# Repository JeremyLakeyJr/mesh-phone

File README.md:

# MESH-PHONE

ESP32-S3 handheld hardware with sub-GHz radios, LTE, NFC/RFID, a 4×4 keypad,
trackball, GPS and a rear expansion connector. Engineering prototype. **DO NOT FABRICATE OR POWER:** the current handset
is incomplete and only partially routed.

## Project layout

| Directory | Contents |
|---|---|
| [hardware/rev-f](hardware/rev-f/README.md) | Preserved GPS/expansion revision; superseded by the handset redesign |
| [hardware/handset-rev-a](hardware/handset-rev-a/README.md) | Active handset PCB and schematic; open `generated/handset.kicad_pro` |
| `hardware/main/` | Preserved original KiCad project and its local footprints |
| [mechanical/handset](mechanical/handset/README.md) | Latest reference-inspired handset concept; requires new PCB |
| [mechanical/enclosure](mechanical/enclosure/README.md) | Preserved enclosure for the existing Rev F board |
| `scripts/` | Maintained geometry extraction and revision verification |
| `docs/design/` | Historical design notes, pin budgets and routing notes |
| `docs/reviews/` | Electrical review evidence |
| `manufacturing/` | BOMs and explicitly unreleased legacy fabrication exports |
| `archive/` | Prior PCB candidates, enclosure and one-off development scripts |

## Working with the project

Open `hardware/handset-rev-a/generated/handset.kicad_pro` in KiCad 10.
Keep its local symbol and footprint libraries beside the project. The current
checkpoint was checked with KiCad 10.0.6.

Run `bash scripts/check_handset_pcb.sh` to refresh the native netlist, ERC/DRC,
connectivity checks, schematic PDF and previews. Then run
`python3 scripts/check_handset_release.py` to evaluate the release gate.
**The release gate currently fails intentionally:** passing artifact-integrity
checks does not mean the electronics are ready to manufacture.

For the preserved Rev F project, `python3 scripts/verify_revF.py` checks its saved
netlist and placement contracts; it does not run fresh native electrical analysis.

Run `python scripts/enclosure_geometry.py` after PCB mechanical changes, then
`scripts/export_enclosure.sh` to rebuild the enclosure STLs and preview.
See the mechanical README for panel-placement assumptions and fit checks.

Archived scripts preserve historical experiments, including obsolete absolute
paths and old project names. They are not a supported build pipeline and should
not be replayed on the active board. `.history/` is the existing KiCad history
repository and remains in place.

The current enclosure has a sculpted rear, rounded corners and a rolled front
rim. Its maximum body envelope remains 74 × 154 × 26 mm; populated-board fit
and the detachable modem pod still need engineering validation.

Latest appearance: [handset preview](mechanical/handset/exports/design-preview.png).
See [feature preservation](mechanical/handset/FEATURES.md) for the retained hardware
requirements and explicit packaging changes. Build with `scripts/export_handset.sh`.
The selected new-board materials list is in
[`hardware/handset-rev-a/materials-to-use.csv`](hardware/handset-rev-a/materials-to-use.csv).
The supporting component research and comparison table are in
[`docs/research/new-pcb-component-study.md`](docs/research/new-pcb-component-study.md)
and [`hardware/handset-rev-a/candidate-components.csv`](hardware/handset-rev-a/candidate-components.csv).

## Fabrication readiness checklist

Checkpoint: **2026-10-13**. Checked items mean the stated design-file work is
complete, not that the hardware has passed bench testing. Current status:
**277 schematic components, 2,644 passing integrity checks, zero schematic/PCB
parity findings, 20 ERC findings, zero DRC findings, and
142 unconnected items.** Eleven engineering blocker groups remain open.
The detailed source of truth is
[release-blockers.json](hardware/handset-rev-a/release-blockers.json).

Current priority is prototype fabrication readiness: complete the missing circuits,
finish copper and return paths, clear ERC/DRC, freeze the BOM and mechanical fit,
and obtain fabricator/assembler DFM review. Firmware feature work follows this
hardware work. Bench qualification remains required after prototype assembly.

### Completed design work

- [x] Route SX1262 SPI, chip select and pull-up, reset, BUSY and DIO1. Twelve checks and 17 regression cases pass; native DRC/parity remain clear. [Digital checkpoint](hardware/handset-rev-a/sx1262-power-review.md#digital-interface-checkpoint--2026-10-13).

- [x] Route the CC1101 SPI, chip-select pull-up, GDO0 and GDO2 test point. Thirteen checks and 15 regression cases pass; native DRC/parity remain clear. [Digital checkpoint](hardware/handset-rev-a/cc1101-review.md#digital-interface-checkpoint--2026-10-12).

- [x] Route the SX1262 switch, three RF DC blocks, antenna connector, control filter and filtered supply. Seventeen regression cases and 753 reference samples pass; RF performance remains unqualified. [Switched RF checkpoint](hardware/handset-rev-a/sx1262-power-review.md#switched-rf-routing-checkpoint--2026-10-10).

- [x] Ground all five SX1262 matching-device return lands using scoped 0.2 mm drilled vias and local copper. Thirteen regression cases pass; record a screened 0.34 mm downstream RF routing target. [Ground/impedance checkpoint](hardware/handset-rev-a/sx1262-power-review.md#rf-ground-and-impedance-checkpoint--2026-10-10).
- [x] Relocate the SX1262 clock and route local PA/RF input connections. Nine copper regression cases pass; RF qualification stays open. [Local routing checkpoint](hardware/handset-rev-a/sx1262-power-review.md#local-parf-routing-checkpoint--2026-10-09).
- [x] Capture SX1262 PA choke and dual bypass with specified parts. Eleven circuit mutations pass; PA/RF electrical qualification remains open. [PA checkpoint](hardware/handset-rev-a/sx1262-power-review.md#pa-choke-and-bypass-checkpoint--2026-10-08).
- [x] Capture SX1262 matching/filter, TX/RX switch, control/supply filters and DC blocks. Eight wrong-wiring/value tests pass; physical copper follows in the switched RF checkpoint. [RF checkpoint](hardware/handset-rev-a/sx1262-power-review.md#rf-matching-and-switch-checkpoint--2026-10-08).
- [x] Connect SX1262 input supplies, bypass capacitors and all ground pins to the established rail/return network. Six open-pad tests and 16-pad continuity pass. [Supply checkpoint](hardware/handset-rev-a/sx1262-power-review.md#input-supply-routing-checkpoint--2026-10-08).
- [x] Route the SX1262 core regulator loop, VREG capacitor return and regulator/exposed-pad ground. Six open-pad controls pass; 15 copper items added with existing copper preserved. [Regulator checkpoint](hardware/handset-rev-a/sx1262-power-review.md#regulator-routing-checkpoint--2026-10-08).
- [x] Capture and route the SX1262 TCXO clock: 14 pads, an 8.092 mm relocated clock path and its ground reference pass checks. ERC falls by three; RF frontend and clock electrical qualification remain open. [Clock checkpoint](hardware/handset-rev-a/sx1262-power-review.md#tcxo-clock-checkpoint--2026-10-08).

- [x] Route amplifier power, ground and local shutdown bias; move C13 beside U6. Fifteen physical pads pass continuity, five regression cases pass, and existing copper remains intact. Speaker/I²S/microphone routing remains open. [Layout checkpoint](hardware/handset-rev-a/README.md#audio-power-routing-checkpoint).

- [x] Cross-build an ESP32-S3 keypad bring-up application with I²C, GPIO8 interrupts, USB logs and start/stop/recovery commands. Twelve session tests and native pin-map checks pass. [Build and commissioning instructions](firmware/bringup/README.md); hardware testing remains open.
- [x] Complete the 16-key matrix copper (72 physical pads), add five routing regression cases and a host-tested keypad driver with overflow recovery. [Routing and firmware evidence](hardware/handset-rev-a/keypad-routing-review.md).
- [x] Route ESP32 boot/reset service controls and U2 power, reset, I²C and interrupt connections; eight regression cases pass with zero DRC/parity findings. [Evidence and remaining bring-up work](hardware/handset-rev-a/core-bringup-review.md).
- [x] Organize hardware, mechanical designs, research, reviews and archived checkpoints.
- [x] Create the four-layer handset PCB and rebuild the schematic as a system index plus 24 functional sheets.
- [x] Retain ESP32-S3-WROOM-1-N16R8 and preserve interfaces for the external display, keypad, trackball, cellular adapter, radios, GNSS, NFC/LF RFID, storage, IR, audio and expansion.
- [x] Capture MakerFocus 3000 mAh battery requirements and the external-module connector; exact pack qualification remains below.
- [x] Populate the current schematic/PCB with component footprints and a materials list; final BOM and footprint audits remain below.
- [x] Capture BQ25186 charging, fused USB/battery entry, TPS25200 protection, TUSB320LAI source detection and TCA9536 controls; verify continuity of 113 local power-entry pads.
- [x] Cross-build and validate an inhibited STM32G031 commissioning image with private-bus I²C, PA0 shutdown, watchdog and diagnostic host interface. [Build, evidence and limits](firmware/power/stm32g031/README.md).
- [x] Route supervisor power, private/host I²C and SWD connections; verify 67 endpoints and preserve existing copper. [Routing evidence and remaining work](hardware/handset-rev-a/supervisor-routing-review.md).
- [x] Route charger VSYS to U7, the main power-switch control, and U7 to ESP32 power/bypass/ground; verify 38 physical pads with no new DRC findings. [Routing evidence and limits](hardware/handset-rev-a/main-distribution-review.md).
- [x] Add and route independent STM32 charge permission so a retained expander output cannot defeat reset inhibition; update controller sequencing and pass topology, continuity and fault tests. [Design and qualification limits](hardware/handset-rev-a/charge-inhibit-review.md).
- [x] Capture and place the separate STM32G031 charging supervisor, always-on regulator and isolated host bus; preserve existing copper geometry. [Circuit and remaining work](hardware/handset-rev-a/power-supervisor-review.md).
- [x] Record the charger-policy contract and implement a host-tested portable charger controller with a 4.17 V target; STM32 supervisor integration and hardware tests remain below.
- [x] Capture published MakerFocus pack specifications and calculate an illustrative modem-load budget; the current pack/modem compatibility blocker remains open.
- [x] Audit modem startup/output tolerance and battery current directly from CAD; add regression tests and release-gate checks. User selected a higher-current ~3000 mAh pack; provisional target is at least 5 A, with pack/fit/F2/J1 qualification still open. [Power review and battery requirements](hardware/handset-rev-a/modem-power-review.md).
- [x] Screen a concrete higher-current pouch and low-profile connector: CU-JAS427 and Molex 2053380002. Pack current clears the provisional calculation, but fit and production qualification fail; neither is frozen. [Candidate evidence and remaining checks](hardware/handset-rev-a/battery-candidate-review.md).
- [x] Replace J1 with the low-profile Molex 2053380002 in schematic and PCB; repair local battery/ground routing, preserve unrelated layout, and verify 118 power-entry pads plus a broken-route negative test. [Connector implementation and fuse screening](hardware/handset-rev-a/battery-connector-review.md).
- [x] Widen the battery-to-fuse main trace to 1.2 mm where clearance permits; reduce its calculated resistance by about 24%, preserve placement, and verify continuity with a broken-trace test. Fuse selection and current/thermal qualification remain open. [Copper and fuse follow-up](hardware/handset-rev-a/battery-copper-review.md).
- [x] Inventory handset loads and add a 60-case battery-only power-envelope check separating the charger-fed handset from the modem. Flag the incomplete 0.25 A allowance and configured handset discharge limit in the release gate. [System power review](hardware/handset-rev-a/system-power-review.md).
- [x] Audit display/backlight and expansion limits; specify four high-power backlight resistors in schematic, PCB and BOM. Add checks for panel supply tolerance and port current limit. [Display and expansion review](hardware/handset-rev-a/display-expansion-power-review.md).
- [x] Capture and place a dedicated 3.0 V display supply, SPI/control buffers and touch I²C translator using specified parts. Preserve shared-bus MISO deselection; update BOM and power inventory. Physical routing is recorded below; electrical qualification remains open. [Display interface review](hardware/handset-rev-a/display-interface-review.md).
- [x] Route and physically verify the dedicated display interface: 25 net groups, including supplies, host/connector signals and grounds. Preserve existing placement/copper; add ground returns and continuity regression tests. [Display routing review](hardware/handset-rev-a/display-routing-review.md).
- [x] Install and route the CAT4004A backlight current driver, replacing Q2/R52–R55; verify 26 endpoints, seven regression tests and no new DRC findings. Preserve existing display continuity. [Implementation and qualification limits](hardware/handset-rev-a/backlight-routing-review.md).
- [x] Capture and route expansion power control, fault sensing and hardware signal isolation; verify 31 physical net groups and six regression tests, and add a host-tested portable controller. Preserve all 4,183 existing copper items. [Implementation and qualification limits](hardware/handset-rev-a/expansion-control-review.md).
- [x] Improve expansion ESD ground returns with local inner-layer pours and a direct U16 ground bridge; remove 36.24 mm of ground detours, preserve all signal routing and pass ground-return regression tests. [Evidence and remaining limits](hardware/handset-rev-a/expansion-control-review.md).
- [x] Clear all four USB connector hole-clearance findings using a dedicated ground-corner-relief footprint; preserve holes, routed copper and board rules. Native DRC is now zero; four geometry regression tests pass. [Footprint change and remaining qualification](hardware/handset-rev-a/usb-connector-review.md).
- [x] Route both USB-C data orientations through ESD protection and 22 Ω host termination; match CAD path lengths, add reference copper and verify seven regression cases. Record the JLC04161H-7628 stackup target; fabricator impedance and electrical qualification remain open. [Routing evidence and limits](hardware/handset-rev-a/usb-data-routing-review.md).
- [x] Route the local TPS63802 main 3.3 V regulator circuit; verify continuity of 26 pads.
- [x] Route U20 local modem converter, feedback, ground and switch-controlled enable network; verify 48 pads with no new DRC findings. [Layout and startup limits](hardware/handset-rev-a/modem-layout-review.md).
- [x] Route U10 local 5 V boost, feedback, ground and switch enable; verify 19 pads with no new DRC findings. [Layout and voltage limits](hardware/handset-rev-a/reg5-layout-review.md).
- [x] Route U10 VSYS feed and LF RFID power/ground for U9/U18; verify 36 pads and preserve existing copper. [Distribution evidence and limits](hardware/handset-rev-a/reg5-distribution-review.md).
- [x] Route the local U11 1.8 V regulator circuit, reposition input bypass and orient the inductor toward SW; verify 15 pads and preserve existing copper. [Layout evidence and remaining qualification](hardware/handset-rev-a/reg18-layout-review.md).
- [x] Connect U7 to U11 input, shorten C28 output/sense paths and verify 17 pads. Audit confirms no external 1.8 V loads are assigned; rail purpose remains open. [Distribution evidence](hardware/handset-rev-a/reg18-distribution-review.md).
- [x] Capture auxiliary supplies and the regulated modem supply/enable circuit; complete routing and load qualification remain below.
- [x] Capture the CC1101 clock, 868/915 MHz matching/filter, supply bypass and GDO2 test pad; pass 90 topology/value checks and five negative tests.
- [x] Add SX1262 core DC-DC support, correct its VREG capacitor to 470 nF, and specify input bypass parts; pass 30 circuit checks and four negative tests.
- [x] Capture GNSS, display/touch/backlight, audio, storage/IR, NFC/LF support and protected expansion interfaces; incomplete support circuits are listed below.
- [x] Preserve prior CAD checkpoints and existing routed copper during staged updates.
- [x] Add repeatable checks, schematic PDF and board/assembly previews. Current placement checks report no overlaps; fabrication release remains blocked.

### Remaining before first prototype fabrication

Work through these in order; circuit and mechanical decisions must be resolved
before final routing and manufacturing exports.

- [ ] **Battery and charging:** qualify a higher-current ~3000 mAh 1S replacement (provisional ≥5 A target), preserving the pocketable design; verify dimensions, polarity, protection, NTC and charge/discharge limits. Re-select F2 and qualify J1/harness/copper for the full handset/modem current budget. Complete STM32 durable fault storage, service rearm and expiring host permissions, qualify reset-time CE inhibition and powered-off charging. Confirm NTC attachment and charge-temperature limits. Implement charger policy, fault handling and source recovery; qualify the routed supervisor power/control buses and finish remaining system distribution.
- [ ] **Power supplies:** finish U7 distribution to the remaining peripheral loads and U20 external battery/modem distribution; resolve the audited 3.71–4.13 V turn-on range (up to 4.21 V with the EN-current screening allowance); qualify the routed U10 display branch for voltage, current and trace sizing; resolve the unused 1.8 V rail (assign justified loads or remove it), then finalize U11 output/sense layout. Calculate worst-case inductor current, capacitor DC bias, feedback tolerance, thermal dissipation, startup/UVLO and modem burst margin. Define current-limited bring-up limits and test points.
- [ ] **Cellular adapter:** freeze an orderable modem variant, firmware, SIM interface, logic translation and call-audio circuit. Verify supported bands and carrier VoLTE requirements; interchangeable adapters do not guarantee every carrier. Select the call microphone and speaker/harness arrangement.
- [ ] **SX1262 LoRa:** qualify the captured 32 MHz TCXO amplitude, DIO3 supply and startup timing; qualify the routed PA choke/bypass and local RF input geometry; qualify matching-device grounds, routed RF switch/antenna paths and all three signal-via transitions; complete thermal layout; qualify the routed input supplies and core regulator loop.
- [ ] **CC1101:** qualify shared-SPI/GDO timing, inner-layer return paths and the routed oscillator, bypass, balun/filter and separate antenna feed against the selected stackup. Review crystal load/drive, thermal-via assembly and the optional spur filter; define firmware SPI/GDO configuration.
- [ ] **NFC and LF RFID:** finish ST25R3916B matching/receive circuitry and HTRC110 clock, analog reference, coil network and timing-capable host return path. Specify external coils, crystal loading and tuning provisions.
- [ ] **GNSS:** finish MAX-M10S decoupling and RF feed; select the passive antenna and verify mounting, keepouts and coexistence requirements.
- [ ] **Expansion and USB:** qualify routed J16 current limits, inrush, isolation, ESD return paths, fault recovery and shared-bus timing; integrate the portable controller. Exchange modules only with handset power off. Qualify the routed USB fanout, uncoupled tuning, three via transitions per leg, termination and eye performance; obtain fabricator impedance approval. Obtain assembler DFM approval of the USB4105 relieved ground-land contour and qualify connector fit/solder joints.
- [ ] **Display, controls and peripherals:** next, qualify the routed U28–U31 interface for regulator load/heat, trace sizing, capacitor DC bias, power sequencing and shared-bus timing; qualify the routed CAT4004A backlight current, heat and default-off/on sequencing. Confirm the purchased display/touch configuration, FPC contact orientation, supply/backlight requirements and GPIO budget. Review keypad-scanner controls, shared SPI chip selects, IR boot behavior, microSD and audio interfaces; implement the firmware needed for safe bring-up.
- [ ] **Antennas and coexistence:** select actual LTE, LoRa, CC1101, GNSS and Wi-Fi/BLE antenna arrangements, cable/connectors and matching provisions. Establish ground clearance, spacing and simultaneous-transmit policy; retain access for RF measurements.
- [ ] **BOM and footprints:** freeze all orderable parts with tolerance, voltage, power, dielectric, temperature and lifecycle requirements. Independently audit every custom symbol pin map, package, exposed pad, paste pattern, orientation and connector mating direction. Define DNP options and approved substitutions.
- [ ] **Mechanical fit:** reconcile the PCB with the pocketable case, actual battery, external screen/FPC, trackball opening and retention, top speaker, bottom microphone, antennas, mounting hardware and external module port. Check populated heights, cable bends and moved power-switch access using a full assembly model and fit prototype.
- [ ] **Fabricator rules:** confirm the proposed JLC04161H-7628 four-layer stackup, copper weights, impedance targets, drill/via limits, solder-mask rules and ESP32 and expansion J16.8/U14.1/U14.6/U16.1 via-in-pad filling/capping requirements with the chosen fabricator. Resolve RF reference via sizes against those capabilities.
- [ ] **Complete PCB routing:** connect all 142 currently unconnected items; finish return planes, ground stitching, thermal paths and supply distribution. Review switching loops, RF/USB impedance, antenna keepouts and analog/digital interference. Recheck clearances after all placement changes.
- [ ] **Independent electrical review:** check every pin and power state against manufacturer documents, including boot straps, pull resistors, power sequencing, unpowered interfaces and test access. Close each blocker with evidence rather than marking an incomplete subsystem complete.
- [ ] **Final native checks:** regenerate netlist/ERC/DRC from the exact release revision; resolve the 30 current ERC findings and all airwires; retain zero DRC findings. Require zero parity errors and passing circuit/continuity checks. Any genuinely intentional rule exception needs a documented engineering justification, not a blanket waiver.
- [ ] **Prototype manufacturing package:** export and inspect Gerbers, plated/non-plated drill files, fabrication drawing/stackup, assembly drawings, full MPN BOM, DNP list and pick-and-place files. Verify units, origin, bottom-side rotation, pin 1, polarity and layer alignment in an independent viewer; obtain fabricator/assembler DFM feedback.
- [ ] **Prototype release:** review the complete package and bring-up plan, close the applicable prototype blockers, tag the exact Git revision and archive checksums/reports with the exports. Update the release gate to distinguish an approved prototype from production qualification. Only then authorize a small prototype build.

### After prototype assembly, before production release

These require physical hardware and therefore cannot be prerequisites for
fabricating the first engineering prototypes.

- [ ] Inspect assembly and check shorts/polarity before applying power; bring up each rail on a current-limited supply with the battery initially disconnected.
- [ ] Measure charge limits, NTC/fault response, protected-pack behavior, powered-off charging, source switching, sleep current, runtime, rail stability, thermal rise and worst-case modem/radio bursts.
- [ ] Validate oscillator startup/frequency/drive, LoRa and CC1101 conducted power/sensitivity, spurious emissions, antenna matching and RF coexistence in the assembled case; tune NFC/LF coils and verify GNSS reception.
- [ ] Test calls/SMS/data with the selected adapters and supported carriers, SIM operation, call/media audio, display/touch, keypad combinations, trackball, storage, IR, GNSS/PPS and expansion functions.
- [ ] Test USB/expansion faults and ESD response, power interruption/recovery, firmware update/recovery and repeated accessory connection cycles.
- [ ] Validate enclosure fit, connector access/retention, drops, pocket pressure, temperature and battery protection from mechanical damage.
- [ ] Complete required EMC/radio/product compliance assessment and testing for intended markets and operating modes.
- [ ] Correct prototype findings, repeat affected checks/tests, freeze production BOM/firmware and create assembly test fixtures, programming instructions, acceptance limits and traceability records.
- [ ] Obtain independent final review and release a versioned production manufacturing package only after all qualification evidence is recorded.

Battery follow-up: [pack, charging and power-budget review](hardware/handset-rev-a/battery-charging-review.md).

Implementation evidence: [power entry](hardware/handset-rev-a/power-entry-review.md),
[3.3 V layout](hardware/handset-rev-a/3v3-layout-review.md),
[schematic rebuild](hardware/handset-rev-a/schematic-rebuild-review.md),
[CC1101](hardware/handset-rev-a/cc1101-review.md), and
[SX1262 power](hardware/handset-rev-a/sx1262-power-review.md).

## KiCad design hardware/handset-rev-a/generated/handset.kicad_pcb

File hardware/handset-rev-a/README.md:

# Handset Rev A — PCB redesign in progress

Open [generated/handset.kicad_pro](generated/handset.kicad_pro) in KiCad 10.
This is a new board and hierarchical schematic, not the old Rev F layout.
**It is incomplete, partially routed, and not ready to fabricate or power.**
The original Rev F project is preserved in `../rev-f/`.

Latest: [SX1262 digital interface routing](sx1262-power-review.md#digital-interface-checkpoint--2026-10-13). Fabrication
readiness takes priority over additional firmware features. RF, NFC/LF and other
unfinished circuits remain fabrication blockers.

## Implemented in the design files

- 66 × 142 × 1.6 mm board with four copper layers, four 2.2 mm mounting
  holes and a 27 × 24 mm trackball opening. The extra 4 mm length prevents
  the mounting drills from breaking through the former 138 mm outline.
- Retained ESP32-S3-WROOM-1-N16R8; PSRAM pads 28–30 stay unconnected.
- A rebuilt system index and 21 functional schematic sheets, including
  GNSS/antennas, NFC, protection, storage/IR, LF support, display and modem power.
  See [schematic PDF](generated/handset-schematic.pdf) and
  [rebuild review](schematic-rebuild-review.md) for corrections and remaining work.
- Sixteen switches at the enclosure coordinates, TCA8418 scan circuit,
  matrix row traces on F.Cu and column traces on In2.Cu. Scanner fanout remains.
- BQ25186 programmable charger, TPS63802 3.3 V converter, TPS62840 1.8 V converter,
  TPS61023 LF/backlight 5 V converter and MAX17048 gauge circuits.
- Fused battery and USB paths, TPS25200 eFuse, TUSB320LAI Type-C detection,
  TLV704 always-on detector supply and TCA9536 charge controls. The 113-pad
  local power-entry cell passes copper continuity; firmware and external
  distribution are unfinished. See [power-entry-review.md](power-entry-review.md).
- Main 3.3 V converter local copper is routed and continuity-checked across
  U7, L1, C20–C22 and R30–R33. External power distribution remains incomplete;
  see [3v3-layout-review.md](3v3-layout-review.md).
- CC1101 clock, filtered supply and 868/915 MHz balun/matching/filter circuit
  are captured with specified parts. Crystal, bias, filtered supply, six separate
  bypass branches, masked thermal vias and RF matching/antenna copper are routed
  and checked. Digital routing and RF qualification remain; see [cc1101-review.md](cc1101-review.md).
- SX1262 TCXO clock and local routing are captured; its RF frontend and
  electrical qualification remain open. HTRC110 clock/analog/coil circuits are incomplete.
- MAX98357A media amplifier, SPH0645 digital mic, separate analog call-audio
  harnesses, native ESP32 USB-C and dedicated modem/expansion connectors.
- Manufacturer-derived custom pin definitions and TPS63802 DLA0010A land
  pattern. Custom library geometry still needs an independent pre-fab review.
- MAX-M10S GNSS; ST25R3916B NFC and oscillator; TPS2553 expansion current
  limiter and TPD4E05U06 protection arrays; Hirose DM3D-SF microSD socket;
  LF level translators; transistor-driven case-mounted IR; top-contact
  display connector/backlight switch; TPS63070 regulated modem supply.
- Routed TCA9537 expansion control, SN74CB3Q3245 signal isolation and SN74HCS10 fault interlock; portable controller host tests pass. [Design and remaining qualification](expansion-control-review.md).
- Named Coilcraft XFL4020 inductors replace the generic inductor allowances.
  Details and outstanding electrical work: [population-review.md](population-review.md).

The current component count, native ERC/DRC findings, remaining airwires and
schematic-to-board integrity results are in
[generated/verification-summary.json](generated/verification-summary.json).
The seven former reservation rectangles have been replaced by physical parts
and schematic circuits. Zero reservation rectangles does **not** mean that the
circuits are complete or that the PCB can be ordered.

## Critical unfinished work

| Block | Required work before release |
|---|---|
| GNSS | MAX-M10S is populated. Finish its RF feed, decoupling placement and coexistence review; no hardware backup supply is implemented. |
| Cellular | Select exact unlocked modem/firmware and establish calls, SMS and data on target carriers. The detachable adapter needs its own SIM, antenna feeds, voltage translation, regulated peak-current supply and audio implementation. |
| LCD / touch | ER-TFT024IPS-3 pinout and FH12A-50S-0.5SH(55) connector are captured with backlight switching. Confirm purchased CTP configuration, rail tolerances, FPC orientation/bending and firmware. |
| NFC | ST25R3916B, crystal and bypass components are populated. Finish and tune the antenna matching/receive network and validate oscillator loading. |
| Radio frontends | SX1262 input supply/ground and local core DC-DC loop are routed; finish thermal layout and qualify supply integrity; qualify the relocated TCXO, routed PA and local RF input geometry; qualify matching-device ground vias and the routed switch/antenna path. Qualify the routed CC1101 clock, decoupling, balun/filter, separate antenna feed and digital interface. Finish the remaining radio/peripheral digital routing. |
| LF RFID | SN74AHCT125 and SN74LVC1G17 translation is populated. Clock, analog reference, coil network and timing-capable host return path remain incomplete. |
| GPIO budget | Confirm scanner GPIO behavior and LCD D/C throughput. IR_RX now uses ESP32 GPIO3; preserve default JTAG eFuse policy and verify boot behavior with active IR. |
| USB / J16 | TPS2553 and signal ESD arrays are captured. Finish protected routing, VBUS protection and power-off accessory policy; test current limit and ESD response. |
| Storage / IR | DM3D-SF and IR driver/harnesses are captured. Validate card access, TSAL6400/TSOP38438 case mounting and firmware. |
| Mechanical / RF | Check actual populated heights, display FPC bends, antenna keepouts, connector mating direction and trackball retention. Power-switch placement has moved and needs matching case access. |
| Layout | Finish placement, reference-plane design, all remaining routing, controlled impedance, thermal copper, ground stitching and silkscreen. Clear native ERC/DRC. |

## Power and connector contracts

J1 is a provisional two-pin battery connector; verify the purchased MakerFocus
pack polarity and plug before populating it. J2 is an external 10 kΩ B3435
thermistor to be thermally coupled to the battery; the two-wire pack itself does
not supply that signal. The BQ25186 CE input defaults off; firmware must apply
and read back [charger-policy.json](charger-policy.json) before charging.
The contract requests 300 mA charge on enumerated legacy USB or 500 mA on
qualified Type-C sources, subject to source and thermal limits. It is not yet
implemented firmware. Validate pack protection and discharge current; the
modem burst budget and powered-off charging remain unresolved.

SW19 controls converter enables. VSYS, charger, and battery gauge can remain
energized while the handset rails are off. Inductors now have exact XFL4020
MPNs and documented land patterns; rated-current and thermal review remains.
The legacy-named +5V_RF rail now also supplies the display backlight.

J16 preserves Rev F pin order: GND, EXP_3V3, SCL, SDA, SCK, MOSI, MISO, CS,
IRQ, GND. It is a locking JST GH cable port, independent of the modem.
U14 now supplies EXP_3V3 through a TPS2553 with a 100 kΩ limit resistor;
U15/U16 protect the seven signals. This is captured circuitry, still unrouted
and untested. Swap accessories with power off.

J8 is the proposed modem adapter's 3.3 V logic contract: GND, host TX, host RX,
LTE_ON, GND, MODEM_STATUS. Raw modem UART pins must not be connected unless
their voltage levels match; translation belongs on the adapter. J9 reserves a
separate regulated modem supply with two supply and two ground contacts.
U20 now generates nominal 3.792 V from VBAT, with hardware shutdown and
conservative battery UVLO; it does not connect the modem to raw charger SYS.
Startup requires a sufficiently charged battery (about 3.92 V nominal).
Connector/contact current, cable resistance and transient limits are not yet
validated. J4 carries adapter call speaker ± and microphone ±.
J7 is a proposed harness for PIM447, not a claim that its pad order matches it.

## Multi-carrier requirement

The user requires unlocked operation across carriers. A7672G is consequently
**a candidate, not a frozen or universally compatible modem**. Quectel EG25-G
is another research lead with broader published carrier documentation, but
carrier data approval does not establish smartphone VoLTE acceptance. No
universal-carrier claim is made, and no carrier-specific module is hard-wired
into this main board. The replaceable modem adapter preserves that choice.

## Reproduce and inspect

Edit the saved project directly. `scripts/build_handset_pcb.py` refuses to
overwrite an existing board. The additive population scripts are one-shot
migrations with snapshots/markers; do not rerun them to reset manual placement.

Run `bash scripts/check_handset_pcb.sh` for native XML
netlist export, ERC, DRC, integrity checks and SVG previews. Integrity checks verify real exported
schematic pin nets against board pads and mounting/key coordinates. Passing
them does not waive native errors or establish electrical functionality.

Run `python scripts/check_handset_release.py` for the separate release gate.
It intentionally fails while native errors, unrouted connections or engineering
blockers remain. See [population-review.md](population-review.md) for the
22 September checkpoint and remaining work by review category.

## Primary design references

- [TI BQ25186](https://www.ti.com/lit/ds/symlink/bq25186.pdf)
- [TI TPS63802, including DLA0010A land pattern](https://www.ti.com/lit/ds/symlink/tps63802.pdf)
- [TI TPS62840](https://www.ti.com/lit/ds/symlink/tps62840.pdf)
- [TI TPS61023](https://www.ti.com/lit/ds/symlink/tps61023.pdf)
- [TI TCA8418](https://www.ti.com/lit/ds/symlink/tca8418.pdf)
- [TI CC1101](https://www.ti.com/lit/ds/symlink/cc1101.pdf)
- [Analog Devices MAX17048](https://www.analog.com/media/en/technical-documentation/data-sheets/MAX17048-MAX17049.pdf)
- [u-blox integration-document availability](https://content.u-blox.com/sites/default/files/documents/UBX-M10050-KB_IP_IN_UBX-22012688-2.pdf)
- [SIMCom A7672G specifications and certification list](https://www.simcom.com/product/A7672G.html)
- [Quectel EG25-G carrier and software documents](https://www.quectel.com/product/lte-eg25-g/)

## Audio power routing checkpoint

2026-10-08: U6 supply pins, exposed-pad/ground pins, C13/C14 bypass network and
R13 local shutdown bias now pass physical continuity checks. C13 moved from
(82, 83) mm to (77.45, 80.9) mm, rotated 90 degrees, to put its 100 nF bypass
beside U6. No other footprint, previous track/via, stackup or design rule changed.
All 613 pre-existing connected pad groups retain continuity; all 9,075 previous
copper items remain. The original checkpoint is archived at
`archive/handset-before-audio-routing/a31246005c3d/` in the repository root.

The [MAX98357A datasheet, page 33](https://www.analog.com/media/en/technical-documentation/data-sheets/MAX98357A-MAX98357B.pdf)
specifies supply bypassing and low-resistance supply/output/ground paths.
This routing uses a 0.5 mm feed to the existing 3.3 V trunk, a 0.3 mm bulk-capacitor
branch and short 0.25 mm VDD pad escapes. It is a CAD continuity checkpoint;
current capacity, ground-return/thermal performance, supply noise and audio
performance still need engineering qualification. The 3.3 V system load budget
remains open.

[Construction and preservation evidence](generated/audio-routing.json),
[15-pad continuity checks](generated/audio-routing-check.json) and
[five routing regression cases](generated/audio-routing-tests.json) are included
in the board checks. The release gate checks the new copper directly.
Native DRC and schematic parity are zero; unconnected items fall from 250 to 238.
Thirty ERC findings and eleven engineering blocker groups remain open.

Speaker output placement/routing, I²S, the U2 MEDIA_EN connection and the microphone
are still unfinished. Complete the speaker placement review before routing its
switching-current paths. The circuit is not ready for power-up or fabrication.

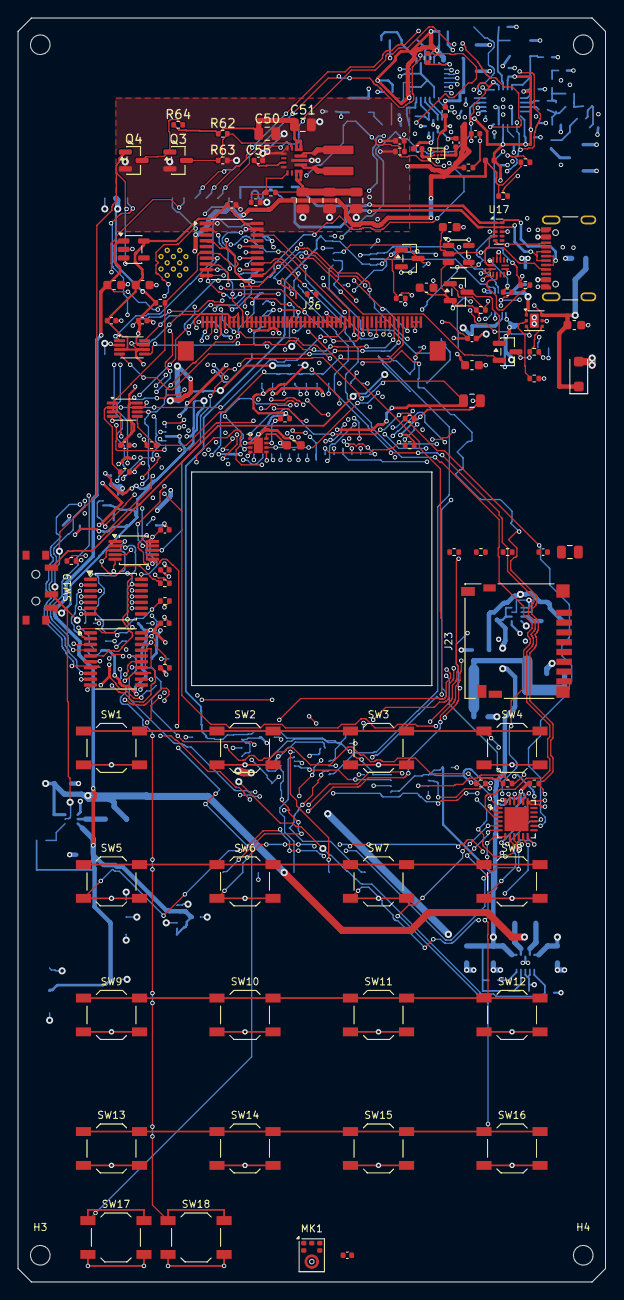
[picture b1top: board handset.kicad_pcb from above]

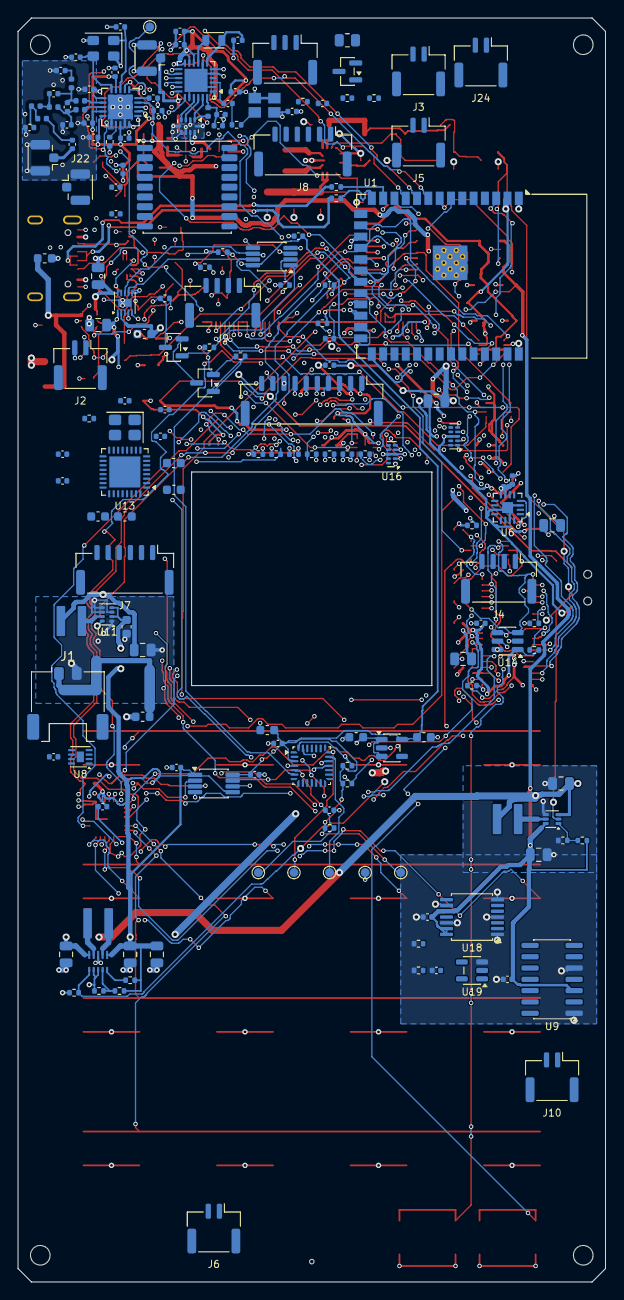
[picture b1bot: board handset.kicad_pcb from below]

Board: 4 copper layers, 66.0 x 142.0 mm, 281 parts (168 on the bottom side), 196 nets.

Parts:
C1, C30, C37, C44: 1uF; C_0402_1005Metric
C2, C14, C20, C25, C28, C41, C43, C49: 10uF; C_0805_2012Metric
C3, C4, C13, C15, C23, C24, C29, C31, C40, C42, C45, C46, C47, C55: 100nF; C_0402_1005Metric
C5: 2.2uF 25V X7R; C_0805_2012Metric
C6: 10uF 25V X5R; C_0805_2012Metric
C7: 4.7uF 10V X7R; C_0603_1608Metric
C8, C11, C12, C69, C70, C71, C72, C73, C75, C76, C79, C81, C82, C83, C86, C87, C88, C89, C91, C92, C93, C94: 100nF 10% X7R 16V; C_0402_1005Metric
C9: 470nF 10% X5R 10V; C_0402_1005Metric
C10: 47nF 10% X7R 25V; C_0402_1005Metric
C21, C22, C26: 22uF; C_0805_2012Metric
C27, C48: 4.7uF; C_0603_1608Metric
C32, C33, C34, C35: 2.2uF; C_0603_1608Metric
C36: 10nF; C_0402_1005Metric
C38, C39: 27pF C0G; C_0402_1005Metric
C50, C51: 10uF 10V X7R; C_0805_2012Metric
C52, C53, C54: 22uF 10V X5R; C_0805_2012Metric
C56, C59: 100nF 50V X7R; C_0603_1608Metric
C57: 2.2uF 10V X7R; C_0603_1608Metric
C58, C60: 100nF 10V X7R; C_0402_1005Metric
C61, C62: 15pF 5% C0G 50V; C_0402_1005Metric
C63: 1pF 0.25pF C0G 50V; C_0402_1005Metric
C64, C68: 1.5pF 0.25pF C0G 50V; C_0402_1005Metric
C65: 3.3pF 0.25pF C0G 50V; C_0402_1005Metric
C66, C98, C99, C100: 100pF 5% C0G 50V; C_0402_1005Metric
C67: 12pF 5% C0G 50V; C_0402_1005Metric
C74: 1uF 10% X5R 10V; C_0402_1005Metric
C77, C78, C80, C84, C85: 4.7uF 10% X5R 25V; C_0603_1608Metric
C90: 1uF 10% X7R 25V; C_0603_1608Metric
C95: 10pF 5% C0G 50V; C_0402_1005Metric
C96, C97: 1nF 10% X7R 50V; C_0402_1005Metric
C101: 47pF 5% C0G 50V; C_0402_1005Metric
D1: SMF5.0A / Diotec; D_SOD-123F
D2: BAT54C,215; SOT-23
F1, F2: 046701.5NRHF / 1.5A; Fuse_0603_1608Metric
H1, H2, H3, H4: MountingHole_2.2mm_M2
J1: 2053380002; Molex_Pico-Lock_205338-0002_1x02-1MP_P2.00mm_Horizontal
J2: PACK_NTC_10K_B3435; JST_GH_BM02B-GHS-TBT_1x02-1MP_P1.25mm_Vertical
J3: MEDIA_SPEAKER_DIFFERENTIAL; JST_GH_BM02B-GHS-TBT_1x02-1MP_P1.25mm_Vertical
J4: CALL_AUDIO_FROM_MODEM_ADAPTER; JST_GH_BM04B-GHS-TBT_1x04-1MP_P1.25mm_Vertical
J5: CALL_EARPIECE; JST_GH_BM02B-GHS-TBT_1x02-1MP_P1.25mm_Vertical
J6: CALL_MIC; JST_GH_BM02B-GHS-TBT_1x02-1MP_P1.25mm_Vertical
J7: PIM447_HARNESS_VERIFY; JST_GH_BM06B-GHS-TBT_1x06-1MP_P1.25mm_Vertical
J8: MODEM_ADAPTER_3V3_LOGIC; JST_GH_BM06B-GHS-TBT_1x06-1MP_P1.25mm_Vertical
J9: MODEM_POWER_ADAPTER_REQUIRED; JST_GH_BM04B-GHS-TBT_1x04-1MP_P1.25mm_Vertical
J10: LF_COIL_TUNING_REQUIRED; JST_GH_BM02B-GHS-TBT_1x02-1MP_P1.25mm_Vertical
J16: EXPANSION_J16; JST_GH_BM10B-GHS-TBT_1x10-1MP_P1.25mm_Vertical
J20: LORA_915_ANT; U.FL_Hirose_U.FL-R-SMT-1_Vertical
J21: CC1101_915_ANT; U.FL_Hirose_U.FL-R-SMT-1_Vertical
J22: GNSS_PASSIVE_ANT; U.FL_Hirose_U.FL-R-SMT-1_Vertical
J23: DM3D-SF; microSD_HC_Hirose_DM3D-SF
J24: TSAL6400_CASE_LED; JST_GH_BM02B-GHS-TBT_1x02-1MP_P1.25mm_Vertical
J25: TSOP38438_CASE_RX; JST_GH_BM03B-GHS-TBT_1x03-1MP_P1.25mm_Vertical
J26: FH12A-50S-0.5SH(55); FH12A-50S-0.5SH_TopContact
L1: XFL4020-471MEC / 0.47uH; Coilcraft_XFL4020
L2: XFL4020-102MEC / 1uH; Coilcraft_XFL4020
L3: XFL4020-222MEC / 2.2uH; Coilcraft_XFL4020
L4: XFL4020-152MEC / 1.5uH; Coilcraft_XFL4020
L5, L6, L9, L10: 12nH 5%; L_0402_1005Metric
L7, L8: 18nH 5%; L_0402_1005Metric
L11: 1kohm @100MHz; L_0402_1005Metric
L12: 15uH 20%; L_TDK_MLZ2012_h1.25mm
L13: 47nH 2%; L_0402_1005Metric
MK1: SPH0645LM4H-1; Knowles_SPH0645LM4H-6_3.5x2.65mm
Q1, Q3, Q4, Q5, Q7, Q8: AO3400A; SOT-23
Q6: AO3401A; SOT-23
R1, R2, R5, R10, R12, R40, R58, R59, R66, R69: 10k; R_0402_1005Metric
R3, R4, R7, R68, R70: 4.7k; R_0402_1005Metric
R6, R8, R13, R30, R33, R47, R50, R51, R57, R64, R67: 100k; R_0402_1005Metric
R9: 887k 1%; R_0402_1005Metric
R11: 56k 1%; R_0402_1005Metric
R20, R21, R22, R23, R24, R25, R26: 33; R_0402_1005Metric
R31: 560k 1%; R_0402_1005Metric
R32, R35, R41, R61, R63, R65, R80, R81, R85, R93: 100k 1%; R_0402_1005Metric
R34: 732k 1%; R_0402_1005Metric
R42, R76, R77, R78, R87: 10k 1%; R_0402_1005Metric
R43, R44, R45: 47k; R_0402_1005Metric
R46, R49, R56: 100; R_0402_1005Metric
R48: 47 1% 0.125W; R_0805_2012Metric
R60: 374k 1%; R_0402_1005Metric
R62: 390k 1%; R_0402_1005Metric
R79, R83, R84: 4.7k 1%; R_0402_1005Metric
R82: 4.99k 1%; R_0402_1005Metric
R86: 220k 1%; R_0402_1005Metric
R88, R89: 22 1%; R_0402_1005Metric
R90: 220R 1%; R_0402_1005Metric
R91, R92: 100R 1%; R_0402_1005Metric
SW1: 1; SW_SPST_TL3342
SW2: 2; SW_SPST_TL3342
SW3: 3; SW_SPST_TL3342
SW4: 4; SW_SPST_TL3342
SW5: 5; SW_SPST_TL3342
SW6: 6; SW_SPST_TL3342
SW7: 7; SW_SPST_TL3342
SW8: 8; SW_SPST_TL3342
SW9: 9; SW_SPST_TL3342
SW10: 10; SW_SPST_TL3342
SW11: 11; SW_SPST_TL3342
SW12: 12; SW_SPST_TL3342
SW13: 13; SW_SPST_TL3342
SW14: 14; SW_SPST_TL3342
SW15: 15; SW_SPST_TL3342
SW16: 16; SW_SPST_TL3342
SW17: MCU_BOOT; SW_SPST_TL3342
SW18: MCU_EN; SW_SPST_TL3342
SW19: POWER; SW_SPDT_PCM12_EdgeAssembly
TP1: CC_GDO2_TEST; TestPoint_Pad_D1.0mm
TP2: PWR_AON_3V0; TestPoint_Pad_D1.0mm
TP3: GND; TestPoint_Pad_D1.0mm
TP4: PWR_SWDIO; TestPoint_Pad_D1.0mm
TP5: PWR_SWCLK; TestPoint_Pad_D1.0mm
TP6: PWR_NRST; TestPoint_Pad_D1.0mm
U1: ESP32-S3-WROOM-1-N16R8; ESP32-S3-WROOM-1_0.3mm_ThermalDrills
U2: TCA8418RTWR; Texas_RTW_WQFN-24-1EP_4x4mm_P0.5mm_EP2.7x2.7mm
U3: BQ25186DLHR; Texas_DLH0010A_WSON-10-1EP_2.2x2mm_P0.4mm_EP0.9x1.5mm
U4: SX1262IMLTRT; QFN-24-1EP_4x4mm_P0.5mm_EP2.6x2.6mm
U5: CC1101RGPR; CC1101_RGP20_MaskedThermalVias
U6: MAX98357AETE+; TQFN-16-1EP_3x3mm_P0.5mm_EP1.23x1.23mm
U7: TPS63802DLAR; TPS63802_DLA0010A
U8: MAX17048G+T; TDFN-8-1EP_2x2mm_P0.5mm_EP0.8x1.2mm
U9: HTRC11001T; SOIC-14_3.9x8.7mm_P1.27mm
U10: TPS61023DRLR; SOT-563
U11: TPS62840DLCR; VSON-8_1.5x2mm_P0.5mm
U12: MAX-M10S-00B-01; ublox_MAX
U13: ST25R3916B-AQET; VQFN-32-1EP_5x5mm_P0.5mm_EP3.5x3.5mm
U14: TPS2553DBVR; SOT-23-6
U15, U16, U17: TPD4E05U06DQAR; USON-10_2.5x1.0mm_P0.5mm
U18: SN74AHCT125PWR; TSSOP-14_4.4x5mm_P0.65mm
U19: SN74LVC1G17DBVR; SOT-23-5
U20: TPS63070RNMR; TPS63070_RNM0015A
U21: TPS25200DRVR; WSON-6-1EP_2x2mm_P0.65mm_EP1x1.6mm
U22: TUSB320LAIRWBR; Texas_X2QFN-12_1.6x1.6mm_P0.4mm
U23: TLV70433DBVR; SOT-23-5
U24: TCA9536DGKR; VSSOP-8_3x3mm_P0.65mm
U25: STM32G031G8U6; QFN-28_4x4mm_P0.5mm
U26: TPS7A0230PDBVR; SOT-23-5
U27: TCA9800DGKR; VSSOP-8_3x3mm_P0.65mm
U28: TPS7A2030PDBVR; SOT-23-5
U29: SN74LVC244APWR; TSSOP-20_4.4x6.5mm_P0.65mm
U30: SN74LVC2G125DCUR; VSSOP-8_2.3x2mm_P0.5mm
U31: TCA9406DCUR; VSSOP-8_2.3x2mm_P0.5mm
U32: CAT4004AHU2-GT3; CAT4004A_UDFN-8_2x2mm_P0.5mm_EP1x1.73mm
U33: TCA9537DGSR; MSOP-10_3x3mm_P0.5mm
U34: SN74CB3Q3245PWR; TSSOP-20_4.4x6.5mm_P0.65mm
U35: SN74HCS10PWR; TSSOP-14_4.4x5mm_P0.65mm
U36: 0900FM15K0039001E; Balun_Johanson_0900FM15K0039
U37: BGS12WN6E6327; Infineon_PG-TSNP-6-10_0.7x1.1mm_0.7x1.1mm_P0.4mm
USB1: USB4105; USB4105_GroundCornerRelief
Y1: ABM8-27.120MHZ-B2-T; Crystal_SMD_3225-4Pin_3.2x2.5mm
Y2: 26MHz CL10pF; ABM8_3225
Y3: 32MHz TCXO 0.5ppm temp; ECS_TXO_32CSMV_3225

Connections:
+1V8: C28.1, L3.2, U11.8
+3V3: C2.1, C3.1, C4.1, C8.1, C13.1, C14.1, C15.1, C21.1, C22.1, C27.1, C29.1, C30.1, C31.1, C37.1, C40.1, C42.1, C43.1, C46.1, C75.1, C76.1, C81.1, C87.1, C89.1, C91.1, C92.1, C93.1, J7.1, J23.4, L11.1, MK1.5, R1.1, R2.1, R3.1, R4.1, R5.1, R10.1, R12.1, R31.1, R33.1, R40.1, R42.1, R43.1, R44.1, R45.1, R48.1, R49.1, R58.1, R59.1, R86.1, R92.1, U1.2, U2.21, U4.1, U4.10, U4.11, U6.7, U6.8, U7.6, U11.2, U11.4, U12.7, U12.8, U13.1, U13.8, U13.10, U14.1, U19.5, U27.1, U27.5, U30.8, U31.7, U33.10, U34.20, U35.14
+5V_RF: C24.1, C26.1, C45.1, C49.1, C84.1, C90.1, J26.1, R34.1, U9.3, U10.6, U18.10, U18.13, U18.14, U28.1, U32.8
BAT_PACK_POS: F2.1, J1.1
BAT_TS: J2.1, U3.6
CALL_MIC_N: J4.4, J6.2
CALL_MIC_P: J4.3, J6.1
CALL_SPK_N: J4.2, J5.2
CALL_SPK_P: J4.1, J5.1
CC_BAL_N: C63.2, C68.1, L6.2, L8.1
CC_BAL_P: C63.1, C64.1, L5.2, L7.1
CC_CS: R12.2, U1.24, U5.7
CC_DCOUPL: C11.1, U5.5
CC_DC_BLOCK: C67.1, L10.2
CC_GDO0: U1.25, U5.6
CC_GDO2: TP1.1, U5.3
CC_LPF: C65.1, L9.2, L10.1
CC_MATCH: C64.2, L8.2, L9.1
CC_RBIAS: R11.1, U5.17
CC_RF_50R: C67.2, J21.1
CC_RF_N: L6.1, U5.13
CC_RF_P: L5.1, U5.12
CC_SHUNT: C66.1, L7.2
CC_VDD: C12.1, C69.1, C70.1, C71.1, C72.1, C73.1, C74.1, L11.2, U5.4, U5.9, U5.11, U5.14, U5.15, U5.18
CC_X1: C61.1, U5.8, Y2.1
CC_X2: C62.1, U5.10, Y2.3
CHG_ARM: Q8.1, R79.1, U25.6
CHG_CE_N: Q5.3, R6.2, U3.4
CHG_CE_RETURN: Q5.2, Q8.3
CHG_ENABLE: Q5.1, R7.1, U24.1
CHG_I2C_SCL: R76.2, U3.8, U24.6, U25.28
CHG_I2C_SDA: R77.2, U3.7, U24.7, U25.27
EXP_3V3: C41.1, J16.2, R87.1, U14.6
EXP_CS: U1.7, U34.7
EXP_CS_PORT: J16.8, R25.2, U16.2
EXP_FAULT_N: R42.2, U14.4, U33.2, U35.13
EXP_GPIO_SPARE: R85.1, U33.4
EXP_ILIM: R41.1, U14.5
EXP_IO_ARM: R84.1, U33.3, U35.2
EXP_IO_OE_N: R86.2, U34.19, U35.12
EXP_IRQ: U1.8, U34.8
EXP_IRQ_PORT: J16.9, R26.2, U16.4
EXP_MISO: J16.7, R24.2, U16.1
EXP_MOSI: J16.6, R23.2, U15.5
EXP_PWR_EN: R83.1, U14.3, U33.1, U35.1
EXP_SCK: J16.5, R22.2, U15.4
EXP_SCL: J16.3, R20.2, U15.1
EXP_SDA: J16.4, R21.2, U15.2
EXP_SW_CS: R25.1, U34.13
EXP_SW_IRQ: R26.1, U34.12
EXP_SW_MISO: R24.1, U34.14
EXP_SW_MOSI: R23.1, U34.15
EXP_SW_SCK: R22.1, U34.16
EXP_SW_SCL: R20.1, U34.18
EXP_SW_SDA: R21.1, U34.17
GND: C1.2, C2.2, C3.2, C4.2, C5.2, C6.2, C7.2, C8.2, C9.2, C10.2, C11.2, C12.2, C13.2, C14.2, C15.2, C20.2, C21.2, C22.2, C23.2, C24.2, C25.2, C26.2, C27.2, C28.2, C29.2, C30.2, C31.2, C32.2, C33.2, C34.2, C35.2, C36.2, C37.2, C38.2, C39.2, C40.2, C41.2, C42.2, C43.2, C44.2, C45.2, C46.2, C47.2, C48.2, C49.2, C50.2, C51.2, C52.2, C53.2, C54.2, C55.2, C56.2, C57.2, C58.2, C59.2, C60.2, C61.2, C62.2, C65.2, C66.2, C68.2, C69.2, C70.2, C71.2, C72.2, C73.2, C74.2, C75.2, C76.2, C77.2, C78.2, C79.2, C80.2, C81.2, C82.2, C83.2, C84.2, C85.2, C86.2, C87.2, C88.2, C89.2, C90.2, C91.2, C92.2, C93.2, C94.2, C96.2, C97.2, C101.2, D1.2, J1.2, J2.2, J7.2, J7.6, J8.1, J8.5, J9.2, J9.4, J16.1, J16.10, J20.2, J21.2, J22.2, J23.6, J23.SH, J25.2, J26.6, J26.11, J26.12, J26.13, J26.14, J26.15, J26.16, J26.17, J26.18, J26.19, J26.20, J26.21, J26.22, J26.23, J26.24, J26.25, J26.26, J26.27, J26.28, J26.29, J26.30, J26.31, J26.32, J26.43, J26.48, J26.49, J26.50, MK1.2, MK1.3, Q1.2, Q3.2, Q4.2, Q7.2, Q8.2, R7.2, R11.2, R13.2, R30.2, R32.2, R35.2, R41.2, R47.2, R50.2, R51.2, R57.2, R61.2, R63.2, R65.2, R67.2, R68.2, R70.2, R79.2, R80.2, R82.2, R83.2, R84.2, R85.2, R87.2, R93.2, SW17.2, SW18.2, SW19.3, TP3.1, U1.1, U1.40, U1.41, U2.19, U2.25, U3.5, U3.11, U4.2, U4.5, U4.8, U4.20, U4.25, U5.16, U5.19, U5.21, U6.3, U6.11, U6.15, U6.17, U7.2, U7.3, U7.8, U8.1, U8.4, U8.6, U8.9, U9.1, U9.5, U10.4, U11.1, U11.3, U11.5, U11.6, U12.1, U12.10, U12.12, U13.6, U13.12, U13.16, U13.20, U13.21, U13.26, U13.33, U14.2, U15.3, U15.8, U16.3, U16.8, U17.3, U17.8, U18.1, U18.4, U18.7, U18.9, U18.12, U19.3, U20.1, U20.4, U20.10, U20.15, U21.5, U21.7, U22.3, U22.10, U22.11, U23.1, U23.4, U23.5, U24.4, U25.4, U26.2, U27.4, U28.2, U29.1, U29.10, U29.15, U29.17, U29.19, U30.4, U30.7, U31.2, U32.2, U32.9, U33.5, U34.9, U34.10, U34.11, U35.3, U35.4, U35.5, U35.7, U35.9, U35.10, U35.11, U36.2, U36.5, U36.7, U36.9, U36.10, U37.2, USB1.A1, USB1.A12, USB1.B1, USB1.B12, USB1.SH, Y1.2, Y1.4, Y2.2, Y2.4, Y3.1, Y3.2
GPS_HOST_RX: U1.5, U12.2
GPS_HOST_TX: U1.4, U12.3
GPS_PPS: U1.6, U12.4
GPS_RF: J22.1, U12.11
I2C_SCL: J7.4, R3.2, U1.17, U2.23, U8.7, U27.2, U31.8, U33.8, U34.2
I2C_SDA: J7.3, R4.2, U1.18, U2.22, U8.8, U27.3, U31.1, U33.9, U34.3
I2S_BCLK: MK1.4, U1.31, U6.16
I2S_DIN: MK1.6, U1.34
I2S_DOUT: U1.33, U6.1
I2S_LRCLK: MK1.1, U1.32, U6.14
IR_GATE: Q1.1, R46.2, R47.1
IR_LED_A: J24.1, R48.2
IR_LED_K: J24.2, Q1.3
IR_RX: J25.1, R59.2, U1.15
IR_RX_VCC: C44.1, J25.3, R49.2
IR_TX: R46.1, U1.35
KEY_COL0: SW1.2, SW5.2, SW9.2, SW13.2, U2.9
KEY_COL1: SW2.2, SW6.2, SW10.2, SW14.2, U2.10
KEY_COL2: SW3.2, SW7.2, SW11.2, SW15.2, U2.11
KEY_COL3: SW4.2, SW8.2, SW12.2, SW16.2, U2.12
KEY_IRQ: R5.2, U1.12, U2.24
KEY_ROW0: SW1.1, SW2.1, SW3.1, SW4.1, U2.8
KEY_ROW1: SW5.1, SW6.1, SW7.1, SW8.1, U2.7
KEY_ROW2: SW9.1, SW10.1, SW11.1, SW12.1, U2.6
KEY_ROW3: SW13.1, SW14.1, SW15.1, SW16.1, U2.5
LCD_3V0: C47.1, C48.1, C85.1, C86.1, C88.1, J26.7, J26.8, J26.9, J26.35, J26.40, J26.41, J26.42, R81.1, U28.5, U29.20, U31.3, U31.6
LCD_BL_EN: R56.1, U2.14
LCD_BL_GATE: R56.2, R57.1, U32.1
LCD_BL_RSET: R82.1, U32.7
LCD_CS: R58.2, U1.19, U29.6, U30.1
LCD_DC: U2.1, U29.8
LCD_K1: J26.2, U32.3
LCD_K2: J26.3, U32.4
LCD_K3: J26.4, U32.5
LCD_K4: J26.5, U32.6
LCD_RESET: U2.2, U29.11
LF_CLK_5V: U9.8, U18.3
LF_DIN_5V: U9.9, U18.6
LF_DOUT_5V: U9.10, U19.2
LORA_RF_50R: C98.2, J20.1
LTE_HOST_RX: J8.3, U1.36
LTE_HOST_TX: J8.2, U1.37
LTE_ON: J8.4, U2.13
MCU_BOOT: R2.2, SW17.1, U1.27
MCU_EN: C1.1, R1.2, SW18.1, U1.3, U2.20, U33.6
MEDIA_EN: R13.1, U2.4, U6.4
MODEM_DISABLE: Q3.1, Q4.3, R64.2
MODEM_FB: R60.2, R61.1, U20.5
MODEM_L1: L4.1, U20.11
MODEM_L2: L4.2, U20.9
MODEM_REG_EN: Q3.3, R62.2, R63.1, U20.14
MODEM_SUPPLY: C52.1, C53.1, C54.1, J9.1, J9.3, R60.1, U20.7, U20.8
MODEM_VAUX: C55.1, U20.3
NFC_AGDC: C36.1, U13.24
NFC_CS: R40.2, U1.39, U13.29
NFC_IRQ: U2.16, U13.27
NFC_VDD_A: C33.1, U13.7
NFC_VDD_AM: C35.1, U13.11
NFC_VDD_D: C32.1, U13.3
NFC_VDD_RF: C34.1, U13.9, U13.14
NFC_XTI: C38.1, U13.5, Y1.1
NFC_XTO: C39.1, U13.4, Y1.3
PANEL_I2C_SCL: J26.44, U31.5
PANEL_I2C_SDA: J26.45, U31.4
PANEL_LCD_CS: J26.38, U29.14
PANEL_LCD_DC: J26.36, U29.12
PANEL_LCD_RESET: J26.10, U29.9
PANEL_SPI_MISO: J26.33, R80.1, U30.2
PANEL_SPI_MOSI: J26.34, U29.16
PANEL_SPI_SCK: J26.37, U29.18
PANEL_TOUCH_IRQ: J26.46, R81.2, U30.5
PANEL_TOUCH_RESET: J26.47, U29.7
PWR_AON_3V0: C60.1, C78.1, C79.1, C80.1, C82.1, R66.1, R69.1, R76.1, R77.1, R78.1, TP2.1, U24.8, U25.3, U26.5, U27.8
PWR_HOST_SCL: U25.18, U27.7
PWR_HOST_SDA: U25.19, U27.6
PWR_NRST: C83.1, R78.2, TP6.1, U25.5
PWR_SWCLK: TP5.1, U25.21
PWR_SWDIO: TP4.1, U25.20
REG3_FB: R31.2, R32.1, U7.4
REG3_L1: L1.1, U7.9
REG3_L2: L1.2, U7.7
REG3_PG: R33.2, U7.5
REG5_FB: R34.2, R35.1, U10.1
REG5_SW: L2.2, U10.5
REG18_SW: L3.1, U11.7
RFID_CLK: R50.1, U2.18, U18.2
RFID_DIN: R51.1, U2.17, U18.5
SD_CS: J23.2, R44.2, U1.38
SD_DAT1: J23.8, R45.2
SD_DAT2: J23.1, R43.2
SPI_MISO: J23.7, U1.22, U4.16, U5.2, U13.32, U30.6, U34.6
SPI_MOSI: J23.3, U1.21, U4.17, U5.20, U13.31, U29.4, U34.5
SPI_SCK: J23.5, U1.20, U4.18, U5.1, U13.30, U29.2, U34.4
SPK_N: J3.2, U6.10
SPK_P: J3.1, U6.9
SX_ANT_AC: C98.1, U37.5
SX_BUSY: U1.10, U4.14
SX_CS: R10.2, U1.23, U4.19
SX_DCC_SW: L12.1, U4.9
SX_DIO1: U1.11, U4.13
SX_RESET: U1.9, U4.15
SX_RFI_N: U4.22, U36.3
SX_RFI_P: U4.21, U36.4
SX_RFO: L13.2, U4.23, U36.1
SX_RF_SW: R91.1, U4.12
SX_RX_AC: C100.2, U37.3
SX_RX_MATCH: C100.1, U36.6
SX_SWITCH_CTRL: C96.1, R91.2, R93.1, U37.6
SX_SWITCH_VDD: C97.1, R92.2, U37.4
SX_TCXO_COUPLED: C95.1, R90.2
SX_TCXO_OUT: R90.1, Y3.3
SX_TCXO_PWR: C94.1, U4.6, Y3.4
SX_TX_AC: C99.2, U37.1
SX_TX_MATCH: C99.1, U36.8
SX_VREG: C9.1, L12.2, U4.7
SX_VR_PA: C10.1, C101.1, L13.1, U4.24
SX_XTA: C95.2, U4.3
SYS_EN: Q4.1, R30.1, SW19.2, U7.1, U10.2, U28.3
TOUCH_IRQ: U2.15, U30.3
TOUCH_RESET: U2.3, U29.13
USB_AON_3V3: C57.1, C58.1, Q6.2, R8.1, U22.12, U23.3
USB_CC1: U17.4, U22.1, USB1.A5
USB_CC2: U17.5, U22.2, USB1.B5
USB_CC_AUTO: D2.1, Q6.3, Q7.1, R70.1
USB_CC_HIGH_N: Q6.1, R8.2, U22.7
USB_CC_QUALIFIED_N: Q7.3, R69.2, U24.3
USB_D_N: R88.2, U17.1, U17.10, USB1.A7, USB1.B7
USB_D_P: R89.2, U17.2, U17.9, USB1.A6, USB1.B6
USB_FUSED: C56.1, C59.1, D1.1, F1.2, R9.1, U21.6, U23.2
USB_HOST_D_N: R88.1, U1.13
USB_HOST_D_P: R89.1, U1.14
USB_ILIM: R65.1, U21.2
USB_LEGACY_EN: D2.2, R68.1, U24.2
USB_PROTECTED: C5.1, U3.10, U21.1
USB_PWR_EN: D2.3, R67.1, U21.4
USB_PWR_FAULT_N: R66.2, U21.3, U24.5
USB_VBUS: F1.1, USB1.A4, USB1.A9, USB1.B4, USB1.B9
USB_VBUS_DET: R9.2, U22.4
VBAT: C7.1, C23.1, C50.1, C51.1, F2.2, R62.1, R64.1, U3.2, U8.2, U8.3, U20.12, U20.13
VSYS: C6.1, C20.1, C25.1, C77.1, L2.1, R6.1, SW19.1, U3.1, U7.10, U10.3, U26.1, U26.3
